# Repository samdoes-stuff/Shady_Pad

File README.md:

# Shady Pad
It is 3x3 custom sized 8 key macropad for app shortcuts equipped with a 0.91 inch display and EC11 encoder

## Usage
To use, one should flash their xiao rp2040 with the correct circuitpython .uf2 file, upload the code file, as well as libraries and linked images, save, and you're good to go! you can customize what each key does, lighting color, text displays, etc all within the code.py file

## Cad

## PCB

## Schematic

I later did not used LEDs in my PCB
## Firmware
- KMK based,
- Screen used for identifying layers, icon display, and signature display
- Custom rotary encoder decoding software from one analog pin
- Custom Key object designed for the rotary encoder multi function button
- Advanced use of macros and hotkeys for daily use
## BOM
Please refer to BOM.csv

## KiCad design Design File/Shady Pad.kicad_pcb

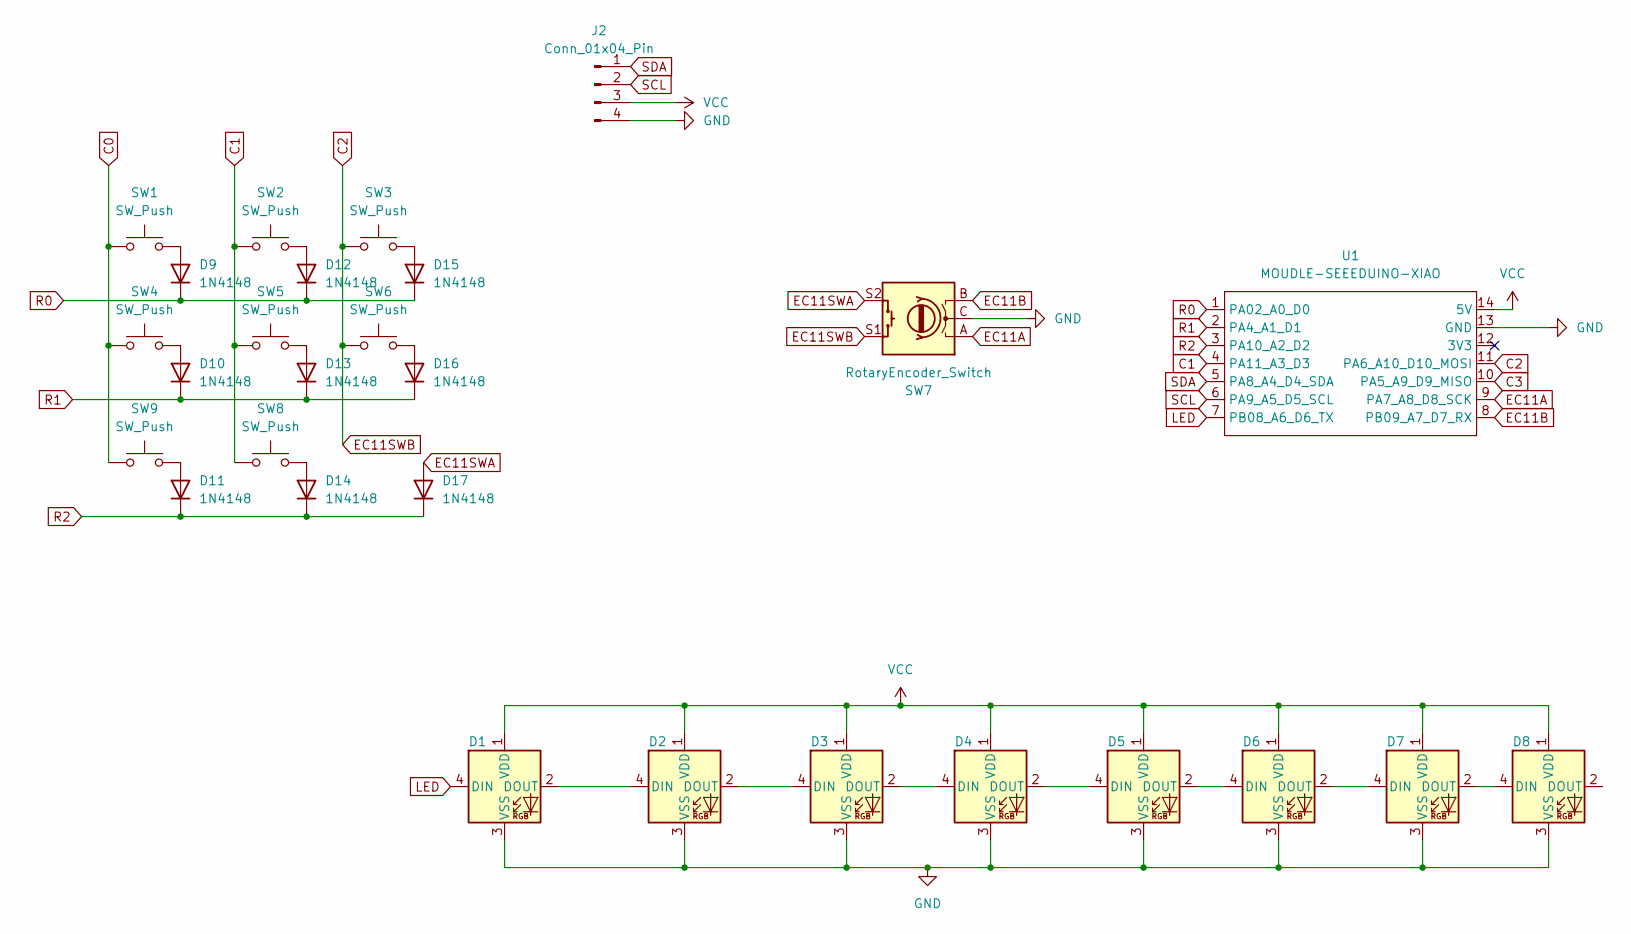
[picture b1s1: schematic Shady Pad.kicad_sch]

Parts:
D1, D2, D3, D4, D5, D6, D7, D8: SK6812MINI-E_fixed
D9, D10, D11, D12, D13, D14, D15, D16, D17: 1N4148; D_DO-35_SOD27_P7.62mm_Horizontal
J2: Conn_01x04_Pin; SSD1306-0.91-OLED-4pin-128x32
SW1, SW2, SW3, SW4, SW5, SW6, SW8, SW9: SW_Push; SW_Cherry_MX_1.00u_PCB
SW7: RotaryEncoder_Switch; RotaryEncoder_Alps_EC11E-Switch_Vertical_H20mm
U1: MOUDLE-SEEEDUINO-XIAO; XIAO-Generic-Hybrid-14P-2.54-21X17.8MM

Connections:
C0: SW1.1, SW4.1, SW9.1
C1: SW2.1, SW5.1, SW8.1, U1.4 (PA11_A3_D3)
C2: SW3.1, SW6.1, SW7.S1, U1.11 (PA6_A10_D10_MOSI)
C3: U1.10 (PA5_A9_D9_MISO)
EC11A: SW7.A, U1.9 (PA7_A8_D8_SCK)
EC11B: SW7.B, U1.8 (PB09_A7_D7_RX)
EC11SWA: D17.2 (A), SW7.S2
GND: D1.3 (VSS), D2.3 (VSS), D3.3 (VSS), D4.3 (VSS), D5.3 (VSS), D6.3 (VSS), D7.3 (VSS), D8.3 (VSS), J2.4, SW7.C, SW7.MP, U1.13 (GND)
LED: D1.4 (DIN), U1.7 (PB08_A6_D6_TX)
unnamed: D1.2 (DOUT), D2.4 (DIN)
unnamed: D2.2 (DOUT), D3.4 (DIN)
unnamed: D3.2 (DOUT), D4.4 (DIN)
unnamed: D4.2 (DOUT), D5.4 (DIN)
unnamed: D5.2 (DOUT), D6.4 (DIN)
unnamed: D6.2 (DOUT), D7.4 (DIN)
unnamed: D7.2 (DOUT), D8.4 (DIN)
unnamed: D9.2 (A), SW1.2
unnamed: D10.2 (A), SW4.2
unnamed: D11.2 (A), SW9.2
unnamed: D12.2 (A), SW2.2
unnamed: D13.2 (A), SW5.2
unnamed: D14.2 (A), SW8.2
unnamed: D15.2 (A), SW3.2
unnamed: D16.2 (A), SW6.2
R0: D9.1 (K), D12.1 (K), D15.1 (K), U1.1 (PA02_A0_D0)
R1: D10.1 (K), D13.1 (K), D16.1 (K), U1.2 (PA4_A1_D1)
R2: D11.1 (K), D14.1 (K), D17.1 (K), U1.3 (PA10_A2_D2)
SCL: J2.2, U1.6 (PA9_A5_D5_SCL)
SDA: J2.1, U1.5 (PA8_A4_D4_SDA)
VCC: D1.1 (VDD), D2.1 (VDD), D3.1 (VDD), D4.1 (VDD), D5.1 (VDD), D6.1 (VDD), D7.1 (VDD), D8.1 (VDD), J2.3, U1.14 (5V)

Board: 2 copper layers, 28 parts (0 on the bottom side), 29 nets, no tracks yet.

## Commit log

2026-03-07 Add BOM.csv with components and quantities
2026-03-07 Update BOM section in README.md
    Removed detailed BOM list and added BOM section header.
2026-03-07 Correct key count and add CAD, PCB, Schematic sections
    Updated the description to reflect the correct number of keys and added sections for CAD, PCB, and Schematic with images.
